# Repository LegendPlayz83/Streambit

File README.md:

# Streambit

This is my 65% Keyboard, which I made from scratch with some help. It is named Streambit.<br>

Physical view:

<br>
A special thanks to Kai, Anay, Mohid, and Souptik, and a big thanks to Alex, who is helping me improve my projects. 💓

# Inspiration
I've always wanted to build a keyboard, and Blueprint gave me the perfect opportunity for this

# Challenges
This was the first time using some new libraries. There were not many big issues, just usage problems which were resolved on Slack <a href="hackclub.slack.com/archives/C0948RT0C1M">Grounded</a>.
<br>
It was sad getting your keyboard rejected. The spirit of getting it approved on the first try is something else.

# Specifications

# Keyboard PCB – Bill of Materials (BOM)

| Component | Quantity | Unit Price       | Total       |
|-----------|----------|------------------|-------------|
| [**TTC Silent Red V3 MX Mechanical Switches**](https://stackskb.com/store/ttc-silent-red-v3-switch/) | 64 | $0.45 | $28.80 |
| [**1N4148 Switching Diodes**](https://amzn.in/d/02ax8rq9) | 100 | $0.0206 | $2.06 |
| [**Cherry MX Plate Mount Stabilizers (2U)**](https://stackskb.com/store/genuine-cherry-mx-plate-mount-stabilizers-2u/) | 4 | $1.30 | $5.20 |
| [**Durock Smokey Screw-In Stabilizers V2 (4+1 w/ 6.25u spacebar)**](https://stackskb.com/store/durock-smokey-screw-in-stabilizers-v2/) | 1 | $18.58 | $18.58 |
| [**EC11 Rotary Encoder with Switch**](https://www.flyrobo.in/15mm-ec11-rotary-encoder-with-switch-digital-potentiometer) | 1 | $0.68 | $0.68 |
| **SK6812 MINI LEDs** | 4  | $2.95 | $2.95 |
| [**Raspberry Pi Zero W**](https://amzn.in/d/4E8fnHk) | 1 | $10.00 | $10.00 |
| [**Iceberg Japanese XDA PBT Keycaps**](https://curiositycaps.in/products/iceberg-japanese-xda-pbt-keycaps-1) | 1 | $25.00 | $25.00 |
| [**Custom PCB (JLCPCB)**](https://jlcpcb.com/) | 1 | $48.86 | $48.86 |
| **Case (From printing-legion)** | 1 | $5.00 | $5.00 |
---

**Grand Total: $147.13**<br>
Others:
<ul>
<li>KMK Firmware
<li>Top Case.stl
</ul>

<h3>Schematic-</h3>

<h3>PCB</h3>

<h3>PCB in 3D view</h3>

<h3>Case</h3>

psst: two keys were placed wrongly dont mind :)

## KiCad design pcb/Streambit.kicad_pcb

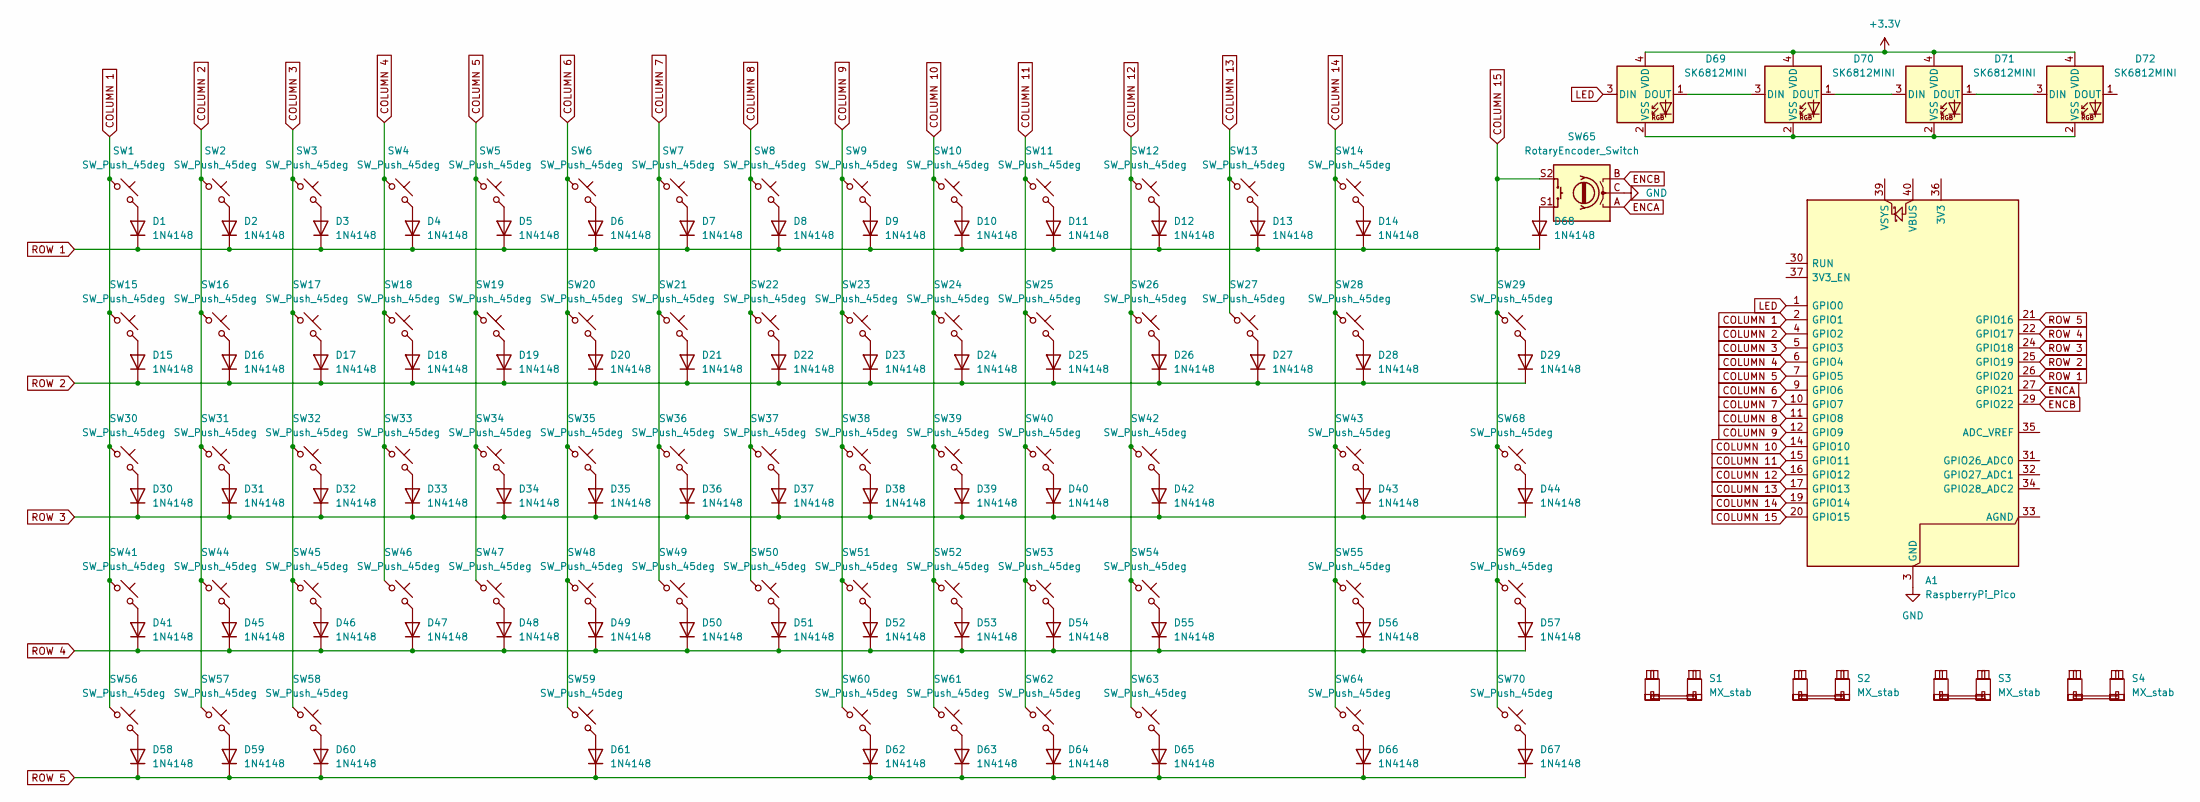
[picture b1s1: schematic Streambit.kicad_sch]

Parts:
A1: RaspberryPi_Pico; RaspberryPi_Pico_SMD_HandSolder
D1, D2, D3, D4, D5, D6, D7, D8, D9, D10, D11, D12, D13, D14, D15, D16, D17, D18, D19, D20, D21, D22, D23, D24, D25, D26, D27, D28, D29, D30, D31, D32, D33, D34, D35, D36, D37, D38, D39, D40, D41, D42, D43, D44, D45, D46, D47, D48, D49, D50, D51, D52, D53, D54, D55, D56, D57, D58, D59, D60, D61, D62, D63, D64, D65, D66, D67, D68: 1N4148; D_DO-35_SOD27_P7.62mm_Horizontal
D69, D70, D71, D72: SK6812MINI; LED_SK6812MINI_PLCC4_3.5x3.5mm_P1.75mm
S1, S2, S3: MX_stab; Stabilizer_Cherry_MX_2.00u
S4: MX_stab; Stabilizer_Cherry_MX_6.25u
SW1, SW2, SW3, SW4, SW5, SW6, SW7, SW8, SW9, SW10, SW11, SW12, SW13, SW14, SW15, SW16, SW17, SW18, SW19, SW20, SW21, SW22, SW23, SW24, SW25, SW26, SW27, SW28, SW29, SW30, SW31, SW32, SW33, SW34, SW35, SW36, SW37, SW38, SW39, SW40, SW41, SW42, SW43, SW44, SW45, SW46, SW47, SW48, SW49, SW50, SW51, SW52, SW53, SW54, SW55, SW56, SW57, SW58, SW59, SW60, SW61, SW62, SW63, SW64, SW68, SW69, SW70: SW_Push_45deg; SW_Cherry_MX_1.00u_PCB
SW65: RotaryEncoder_Switch; RotaryEncoder_Alps_EC11E-Switch_Vertical_H20mm

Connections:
+3.3V: D69.4 (VDD), D70.4 (VDD), D71.4 (VDD), D72.4 (VDD)
COLUMN 1: A1.2 (GPIO1), SW1.1, SW15.1, SW30.1, SW41.1, SW56.1
COLUMN 2: A1.4 (GPIO2), SW2.1, SW16.1, SW31.1, SW44.1, SW57.1
COLUMN 3: A1.5 (GPIO3), SW3.1, SW17.1, SW32.1, SW45.1, SW58.1
COLUMN 4: A1.6 (GPIO4), SW4.1, SW18.1, SW33.1, SW46.1
COLUMN 5: A1.7 (GPIO5), SW5.1, SW19.1, SW34.1, SW47.1
COLUMN 6: A1.9 (GPIO6), SW6.1, SW20.1, SW35.1, SW48.1, SW59.1
COLUMN 7: A1.10 (GPIO7), SW7.1, SW21.1, SW36.1, SW49.1
COLUMN 8: A1.11 (GPIO8), SW8.1, SW22.1, SW37.1, SW50.1
COLUMN 9: A1.12 (GPIO9), SW9.1, SW23.1, SW38.1, SW51.1, SW60.1
COLUMN 10: A1.14 (GPIO10), SW10.1, SW24.1, SW39.1, SW52.1, SW61.1
COLUMN 11: A1.15 (GPIO11), SW11.1, SW25.1, SW40.1, SW53.1, SW62.1
COLUMN 12: A1.16 (GPIO12)
COLUMN 13: A1.17 (GPIO13), SW13.1, SW27.1
COLUMN 14: A1.19 (GPIO14), SW14.1, SW28.1, SW43.1, SW55.1, SW64.1
COLUMN 15: A1.20 (GPIO15), A1.26 (GPIO20), D1.1 (K), D2.1 (K), D3.1 (K), D4.1 (K), D5.1 (K), D6.1 (K), D7.1 (K), D8.1 (K), D9.1 (K), D10.1 (K), D11.1 (K), D12.1 (K), D13.1 (K), D14.1 (K), D68.1 (K), SW29.1, SW65.S2, SW68.1, SW69.1, SW70.1
COLUMN 12: SW12.1, SW26.1, SW42.1, SW54.1, SW63.1
ENCA: A1.27 (GPIO21), SW65.A
ENCB: A1.29 (GPIO22), SW65.B
GND: A1.3 (GND), A1.8 (GND), A1.13 (GND), A1.18 (GND), A1.23 (GND), A1.28 (GND), A1.38 (GND), SW65.C
LED: A1.1 (GPIO0), D69.3 (DIN)
unnamed: D1.2 (A), SW1.2
unnamed: D2.2 (A), SW2.2
unnamed: D3.2 (A), SW3.2
unnamed: D4.2 (A), SW4.2
unnamed: D5.2 (A), SW5.2
unnamed: D6.2 (A), SW6.2
unnamed: D7.2 (A), SW7.2
unnamed: D8.2 (A), SW8.2
unnamed: D9.2 (A), SW9.2
unnamed: D10.2 (A), SW10.2
unnamed: D11.2 (A), SW11.2
unnamed: D12.2 (A), SW12.2
unnamed: D13.2 (A), SW13.2
unnamed: D14.2 (A), SW14.2
unnamed: D15.2 (A), SW15.2
unnamed: D16.2 (A), SW16.2
unnamed: D17.2 (A), SW17.2
unnamed: D18.2 (A), SW18.2
unnamed: D19.2 (A), SW19.2
unnamed: D20.2 (A), SW20.2
unnamed: D21.2 (A), SW21.2
unnamed: D22.2 (A), SW22.2
unnamed: D23.2 (A), SW23.2
unnamed: D24.2 (A), SW24.2
unnamed: D25.2 (A), SW25.2
unnamed: D26.2 (A), SW26.2
unnamed: D27.2 (A), SW27.2
unnamed: D28.2 (A), SW28.2
unnamed: D29.2 (A), SW29.2
unnamed: D30.2 (A), SW30.2
unnamed: D31.2 (A), SW31.2
unnamed: D32.2 (A), SW32.2
unnamed: D33.2 (A), SW33.2
unnamed: D34.2 (A), SW34.2
unnamed: D35.2 (A), SW35.2
unnamed: D36.2 (A), SW36.2
unnamed: D37.2 (A), SW37.2
unnamed: D38.2 (A), SW38.2
unnamed: D39.2 (A), SW39.2
unnamed: D40.2 (A), SW40.2
unnamed: D41.2 (A), SW41.2
unnamed: D42.2 (A), SW42.2
unnamed: D43.2 (A), SW43.2
unnamed: D44.2 (A), SW68.2
unnamed: D45.2 (A), SW44.2
unnamed: D46.2 (A), SW45.2
unnamed: D47.2 (A), SW46.2
unnamed: D48.2 (A), SW47.2
unnamed: D49.2 (A), SW48.2
unnamed: D50.2 (A), SW49.2
unnamed: D51.2 (A), SW50.2
unnamed: D52.2 (A), SW51.2
unnamed: D53.2 (A), SW52.2
unnamed: D54.2 (A), SW53.2
unnamed: D55.2 (A), SW54.2
unnamed: D56.2 (A), SW55.2
unnamed: D57.2 (A), SW69.2
unnamed: D58.2 (A), SW56.2
unnamed: D59.2 (A), SW57.2
unnamed: D60.2 (A), SW58.2
unnamed: D61.2 (A), SW59.2
unnamed: D62.2 (A), SW60.2
unnamed: D63.2 (A), SW61.2
unnamed: D64.2 (A), SW62.2
unnamed: D65.2 (A), SW63.2
unnamed: D66.2 (A), SW64.2
unnamed: D67.2 (A), SW70.2
unnamed: D68.2 (A), SW65.S1
unnamed: D69.1 (DOUT), D70.3 (DIN)
unnamed: D69.2 (VSS), D70.2 (VSS), D71.2 (VSS), D72.2 (VSS)
unnamed: D70.1 (DOUT), D71.3 (DIN)
unnamed: D71.1 (DOUT), D72.3 (DIN)
ROW 2: A1.25 (GPIO19), D15.1 (K), D16.1 (K), D17.1 (K), D18.1 (K), D19.1 (K), D20.1 (K), D21.1 (K), D22.1 (K), D23.1 (K), D24.1 (K), D25.1 (K), D26.1 (K), D27.1 (K), D28.1 (K), D29.1 (K)
ROW 3: A1.24 (GPIO18), D30.1 (K), D31.1 (K), D32.1 (K), D33.1 (K), D34.1 (K), D35.1 (K), D36.1 (K), D37.1 (K), D38.1 (K), D39.1 (K), D40.1 (K), D42.1 (K), D43.1 (K), D44.1 (K)
ROW 4: A1.22 (GPIO17), D41.1 (K), D45.1 (K), D46.1 (K), D47.1 (K), D48.1 (K), D49.1 (K), D50.1 (K), D51.1 (K), D52.1 (K), D53.1 (K), D54.1 (K), D55.1 (K), D56.1 (K), D57.1 (K)
ROW 5: A1.21 (GPIO16), D58.1 (K), D59.1 (K), D60.1 (K), D61.1 (K), D62.1 (K), D63.1 (K), D64.1 (K), D65.1 (K), D66.1 (K), D67.1 (K)

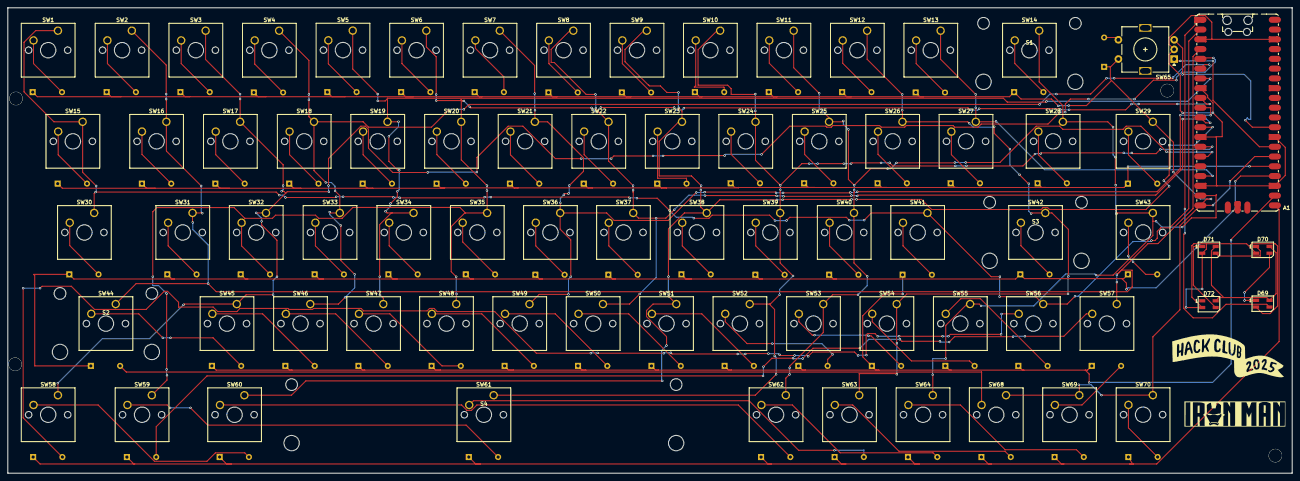
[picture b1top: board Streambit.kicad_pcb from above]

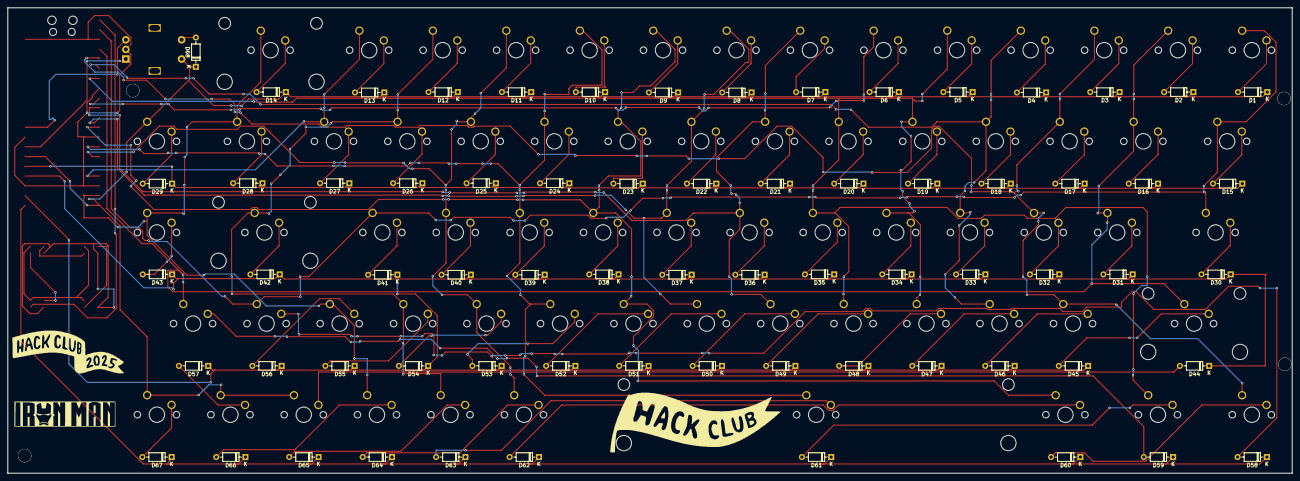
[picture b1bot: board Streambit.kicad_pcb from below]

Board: 2 copper layers, 334.0 x 121.0 mm, 145 parts (68 on the bottom side), 96 nets.

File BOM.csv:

"Id";"Designator";"Footprint";"Quantity";"Designation";"Supplier and ref";
1;"SW30,SW44,SW57,SW2,SW69,SW29,SW51,SW1,SW64,SW41,SW55,SW35,SW20,SW70,SW36,SW43,SW7,SW31,SW46,SW5,SW48,SW25,SW59,SW47,SW27,SW53,SW40,SW56,SW33,SW26,SW45,SW38,SW68,SW13,SW11,SW60,SW62,SW54,SW18,SW24,SW10,SW42,SW28,SW16,SW12,SW3,SW17,SW4,SW37,SW63,SW39,SW32,SW34,SW58,SW8,SW22,SW15,SW19,SW21,SW50,SW61,SW49,SW6,SW23,SW52,SW14,SW9";"SW_Cherry_MX_1.00u_PCB";67;"SW_Push_45deg";;;
2;"S1,S3,S2";"Stabilizer_Cherry_MX_2.00u";3;"MX_stab";;;
3;"A1";"RaspberryPi_Pico_SMD_HandSolder";1;"RaspberryPi_Pico";;;
4;"D71,D72,D70,D69";"LED_SK6812MINI_PLCC4_3.5x3.5mm_P1.75mm";4;"SK6812MINI";;;
5;"S4";"Stabilizer_Cherry_MX_6.25u";1;"MX_stab";;;
6;"SW65";"RotaryEncoder_Alps_EC11E-Switch_Vertical_H20mm";1;"RotaryEncoder_Switch";;;
7;"D27,D63,D62,D28,D21,D54,D37,D36,D52,D7,D33,D45,D53,D58,D41,D40,D24,D6,D38,D1,D19,D49,D25,D13,D68,D60,D61,D18,D10,D8,D14,D9,D29,D55,D39,D2,D16,D65,D44,D26,D50,D5,D15,D30,D23,D56,D46,D32,D31,D67,D20,D34,D4,D66,D57,D43,D3,D51,D17,D12,D59,D42,D22,D11,D64,D35,D47,D48";"D_DO-35_SOD27_P7.62mm_Horizontal";68;"1N4148";;;

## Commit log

2025-08-29 Added files
2026-02-19 Delete BOM.md
    Rather adding bom.csv
2026-02-19 Clarify challenges faced with new libraries
2026-02-20 Rename Bitsteam Case.step to Streambit Case.step
2026-03-09 Revise README with BOM and cost details
    Updated the README to include a detailed Bill of Materials (BOM) and cost summary for the keyboard project.
2026-03-12 Changed images
    Changed images after corrections and making a new case
2026-04-13 Add firmware upload details to JOURNAL.md
    Documented the firmware upload process and time taken.
